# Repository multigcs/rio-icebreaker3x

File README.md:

# rio-icebreaker3x
3 Axis LinuxCNC-RIO adapter-board - for the icebreaker v1.0e FPGA-Devboard - kicad project 

works also on Colorlite_i5 (extboard v1.2)

## software / gateware
https://github.com/multigcs/riocore

## BOM
https://github.com/icebreaker-fpga/icebreaker

## Forum
German: https://www.cnc-aus-holz.at/index.php?thread/3130-experimente-mit-linux-cnc-auf-raspi-und-ice40-fpga-als-mesa-alternative/&postID=40335#post40335
English: https://forum.linuxcnc.org/18-computer/49142-linuxcnc-rio-realtimeio-for-linuxcnc-based-on-fpga-ice40-ecp5

## Videos

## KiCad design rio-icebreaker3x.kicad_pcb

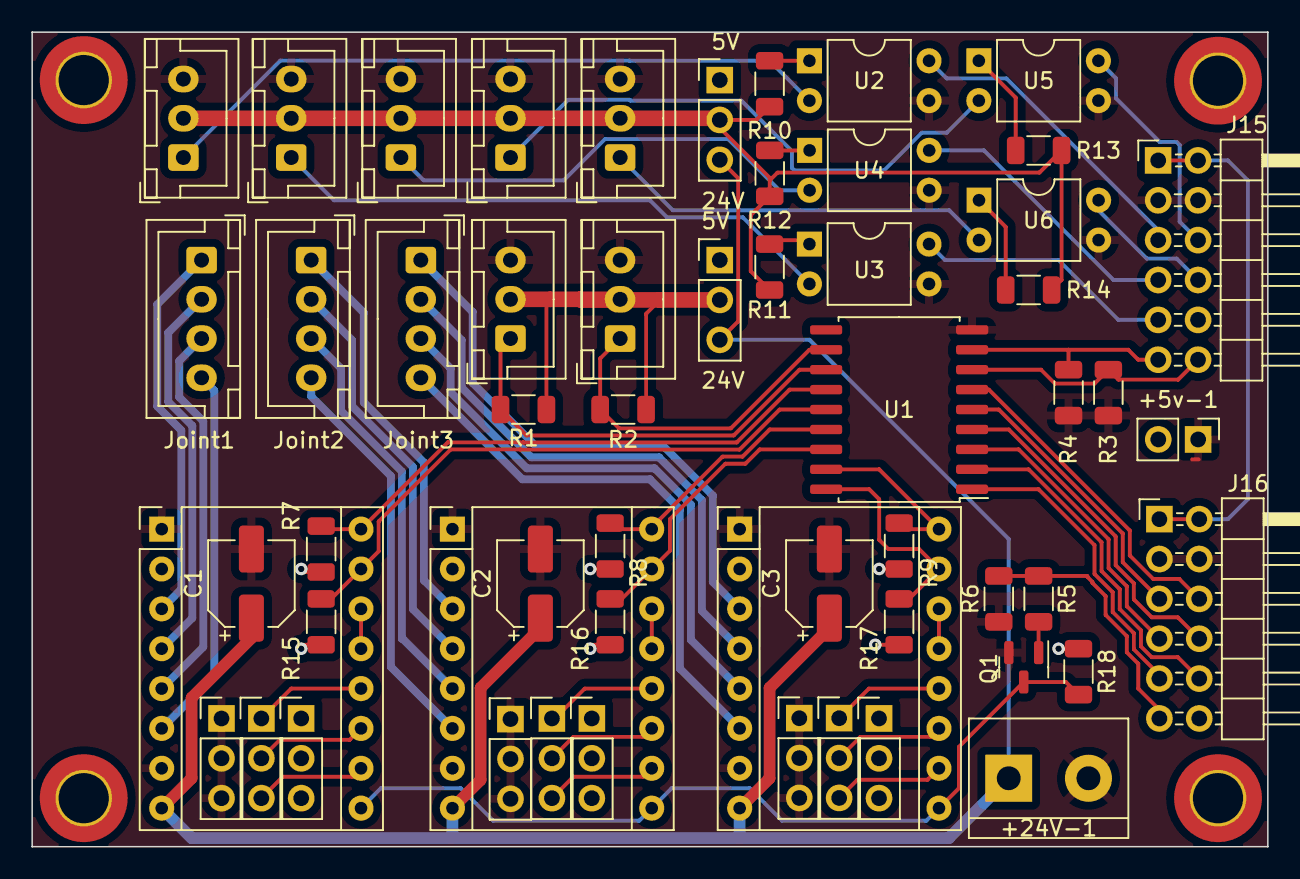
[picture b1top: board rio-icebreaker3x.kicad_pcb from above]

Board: 2 copper layers, 78.7 x 51.9 mm, 60 parts (0 on the bottom side), 64 nets.

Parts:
+5v-1: Conn_01x02; PinHeader_1x02_P2.54mm_Vertical
+24V-1: Screw_Terminal_01x02; TerminalBlock_bornier-2_P5.08mm
A1, A2, A3: Pololu_Breakout_A4988; Pololu_Breakout-16_15.2x20.3mm
C1, C2, C3: C_Polarized; CP_Elec_5x5.9
H1, H2, H3, H4: MountingHole; MountingHole_3.2mm_M3_DIN965_Pad_TopBottom
J1, J2, J3, J4, J5, J6, J7, J8, J9, J10, J11: Conn_01x03; PinHeader_1x03_P2.54mm_Vertical
J15, J16: Conn_02x06_Odd_Even; PinHeader_2x06_P2.54mm_Horizontal
Q1: BC817; SOT-23
R1, R2, R3, R4, R10, R11, R12, R13, R14: R; R_1206_3216Metric
R5: 1k; R_1206_3216Metric
R6: 10k; R_1206_3216Metric
R7, R8, R9, R15, R16, R17, R18: 3k3; R_1206_3216Metric
U1: ULN2803A; SOIC-18W_7.5x11.6mm_P1.27mm
U2, U3, U4, U5, U6: PC817; DIP-4_W7.62mm
input1, input2, input3, input4, input5: Conn_01x03; JST_XH_B3B-XH-A_1x03_P2.50mm_Vertical
out1, out2: Conn_01x03; JST_XH_B3B-XH-A_1x03_P2.50mm_Vertical
stepper1, stepper2, stepper4: Conn_01x04; JST_XH_B4B-XH-A_1x04_P2.50mm_Vertical

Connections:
3v3: J15.1, J15.2, J16.1, J16.2
5v: +5v-1.2, A1.2 (VDD), A2.2 (VDD), A3.2 (VDD), J3.1, J3.2, J3.3, J4.1, J4.2, J4.3, J5.1, J6.1, J9.1, J9.2, J9.3, R7.2, R8.2, R9.2, R15.2, R16.2, R17.2, R18.1
12v: +24V-1.1, A1.8 (VMOT), A2.8 (VMOT), A3.8 (VMOT), C1.1, C2.1, C3.1, J5.3, J6.3
/driver0/dir: A1.16 (DIR), R7.1, U1.13 (O6)
/driver0/enable: A1.9 (~ENABLE), A2.9 (~ENABLE), A3.9 (~ENABLE), Q1.3 (C), R18.2
/driver0/step: A1.15 (STEP), R15.1, U1.14 (O5)
/driver1/dir: A2.16 (DIR), R8.1, U1.15 (O4)
/driver1/step: A2.15 (STEP), R16.1, U1.16 (O3)
/driver2/dir: A3.16 (DIR), R9.1, U1.17 (O2)
/driver2/step: A3.15 (STEP), R17.1, U1.18 (O1)
/input/power: J6.2, R10.2, R11.2, R12.2, R13.2, R14.2, input1.2, input2.2, input3.2, input4.2, input5.2
unnamed: A1.4 (1A), stepper4.2
unnamed: A1.3 (1B), stepper4.1
unnamed: A1.5 (2A), stepper4.3
unnamed: A1.6 (2B), stepper4.4
unnamed: A1.10 (MS1), J1.3
unnamed: A1.11 (MS2), J1.2
unnamed: A1.12 (MS3), J1.1
unnamed: A1.13 (~RESET), A1.14 (~SLEEP)
unnamed: A2.4 (1A), stepper1.2
unnamed: A2.3 (1B), stepper1.1
unnamed: A2.5 (2A), stepper1.3
unnamed: A2.6 (2B), stepper1.4
unnamed: A2.10 (MS1), J8.3
unnamed: A2.11 (MS2), J8.2
unnamed: A2.12 (MS3), J8.1
unnamed: A2.13 (~RESET), A2.14 (~SLEEP)
unnamed: A3.4 (1A), stepper2.2
unnamed: A3.3 (1B), stepper2.1
unnamed: A3.5 (2A), stepper2.3
unnamed: A3.6 (2B), stepper2.4
unnamed: A3.10 (MS1), J11.3
unnamed: A3.11 (MS2), J11.2
unnamed: A3.12 (MS3), J11.1
unnamed: A3.13 (~RESET), A3.14 (~SLEEP)
unnamed: J5.2, R1.1, R2.2, out1.2, out2.2
unnamed: Q1.1 (B), R5.2
unnamed: R10.1, U2.1
unnamed: R11.1, U3.1
unnamed: R12.1, U4.1
unnamed: R13.1, U5.1
unnamed: R14.1, U6.1
unnamed: R1.2, U1.12 (O7), out1.1
unnamed: R2.1, U1.11 (O8), out2.1
unnamed: U2.2, input1.1
unnamed: U3.2, input2.1
unnamed: U4.2, input3.1
unnamed: U5.2, input4.1
unnamed: U6.2, input5.1
dir0: J16.6, U1.6 (I6)
dir1: J16.8, U1.4 (I4)
dir2: J16.10, U1.2 (I2)
en: J16.11, R5.1, R6.2
gnd: +5v-1.1, +24V-1.2, A1.1 (GND), A1.7 (GND), A2.1 (GND), A2.7 (GND), A3.1 (GND), A3.7 (GND), C1.2, C2.2, C3.2, J2.1, J2.2, J2.3, J7.1, J7.2, J7.3, J10.1, J10.2, J10.3, J15.3, J15.4, J16.3, J16.4, Q1.2 (E), R3.1, R4.1, R6.1, U1.9 (GND), U2.3, U3.3, U4.3, U5.3, U6.3, input1.3, input2.3, input3.3, input4.3, input5.3, out1.3, out2.3
in0: J15.5, U2.4
in1: J15.9, U3.4
in2: J15.7, U4.4
in3: J15.6, U5.4
in4: J15.8, U6.4
out0: J15.12, R3.2, U1.7 (I7)
out1: J15.11, R4.2, U1.8 (I8)
step0: J16.5, U1.5 (I5)
step1: J16.7, U1.3 (I3)
step2: J16.9, U1.1 (I1)

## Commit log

2024-07-03 initial release
2024-07-03 adding image
2024-07-10 adding video
2024-07-12 adding missing pullups
2024-07-16 complete tested, works
